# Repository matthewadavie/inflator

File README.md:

# Inflator V3
## Background
I like four wheel driving. I dislike having to sit in the sun to inflate my tyres manually.

Unfortunately the only option (commercially) is on the order of > $300. That is excessive. It can be cheaper.

## Requirements
* Input Voltage: 6V - 18V (nominal)
* Input Voltage: 4V - 30V (transient)
* Functions:
  - HSD/FET gate drive for compressor control & solenoid activation
  - ESP32 for wireless comms (originally wanted STM32 but decided that I would rather control the pressure from webapp on phone)
  - OLED to display pressure readings

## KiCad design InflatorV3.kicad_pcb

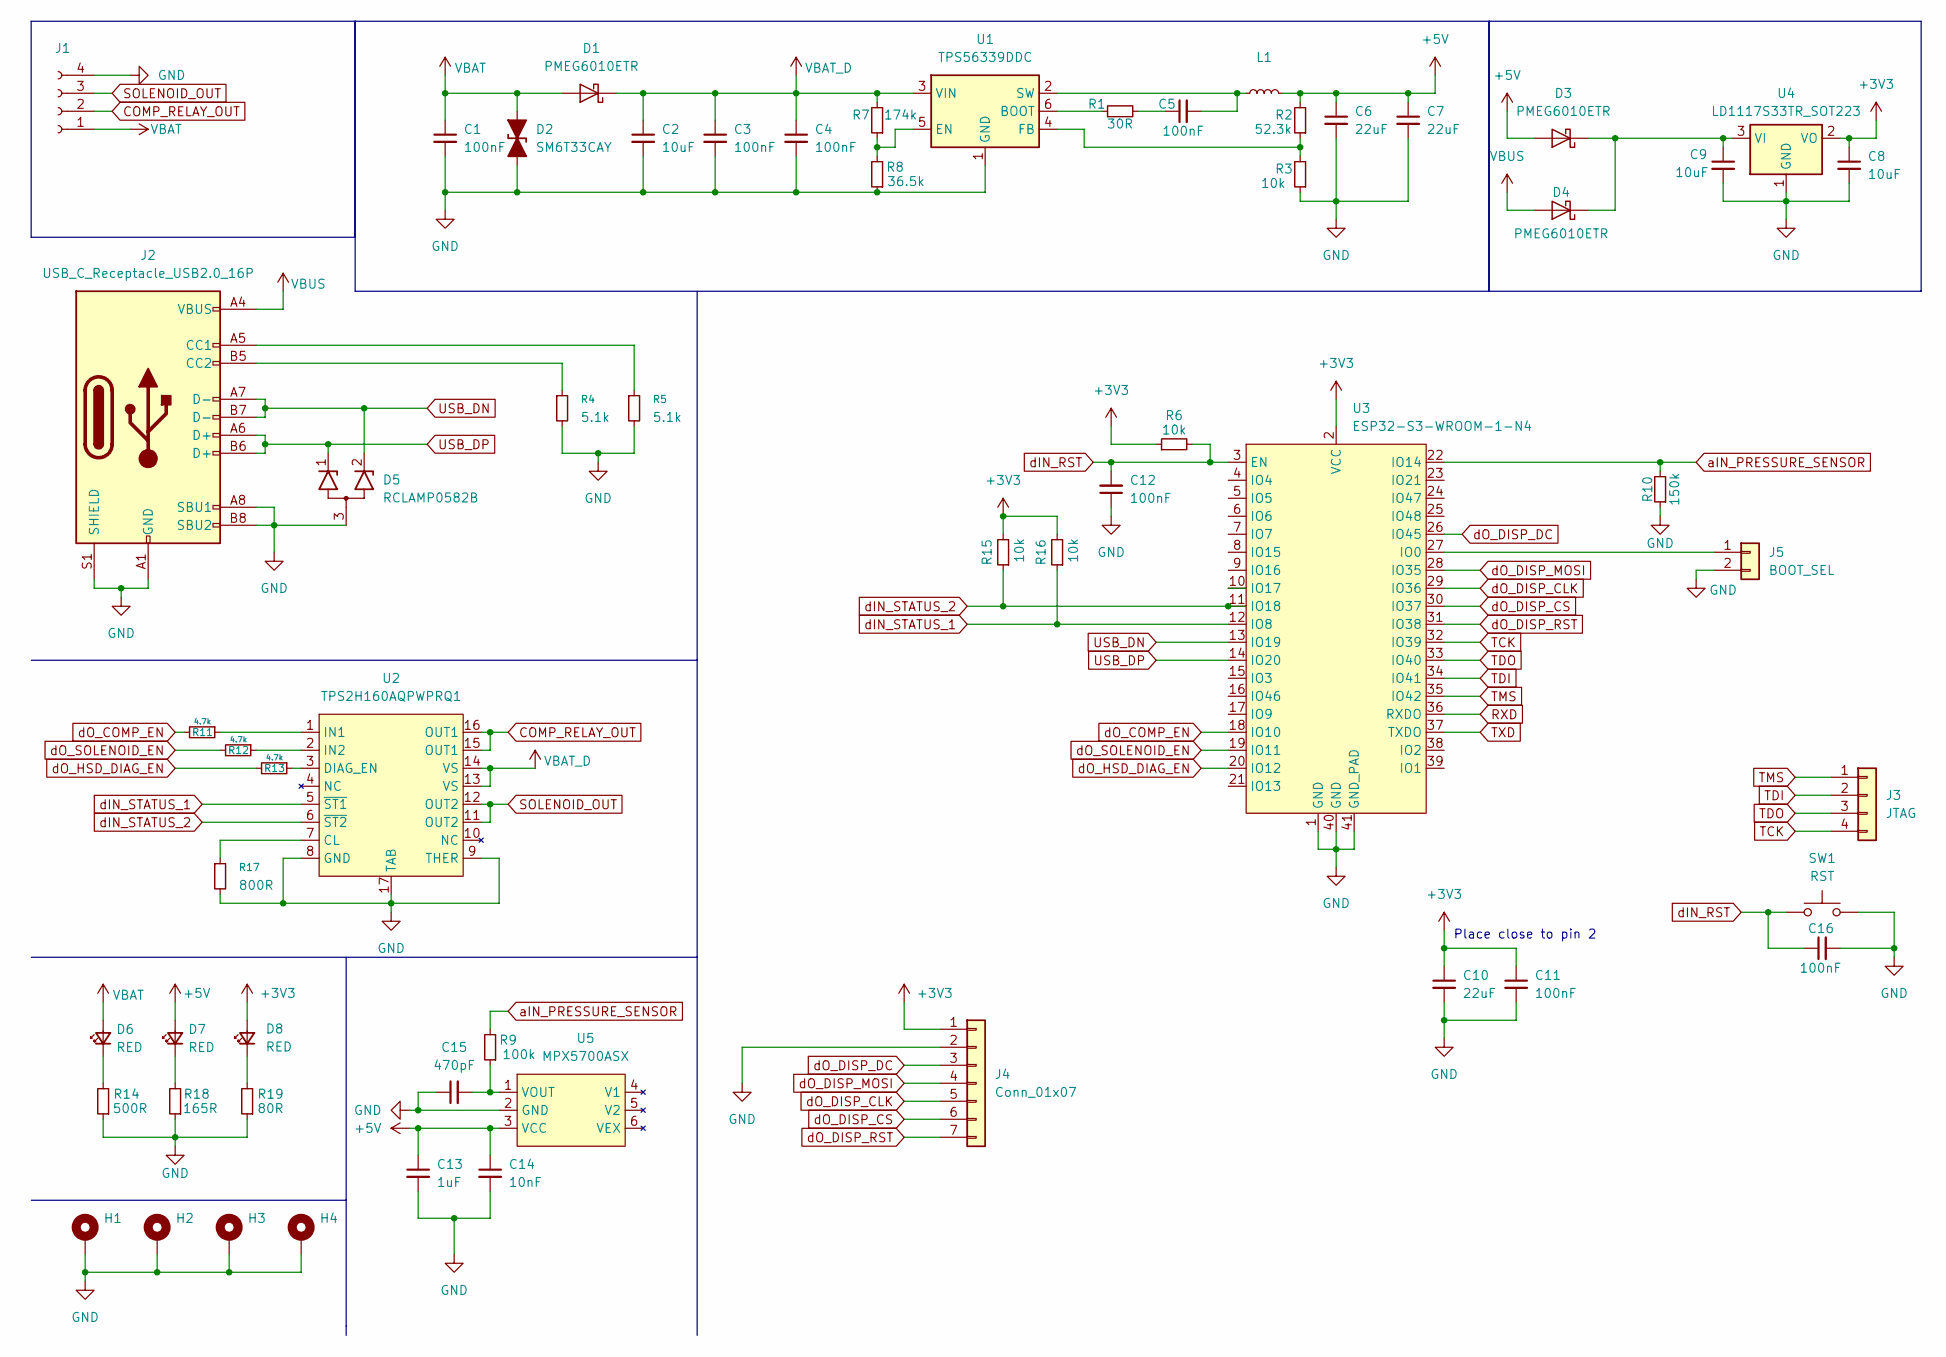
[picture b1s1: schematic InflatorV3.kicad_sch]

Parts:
C1, C11, C12: 100nF; C_1206_3216Metric_Pad1.33x1.80mm_HandSolder
C2: 10uF; C_1206_3216Metric_Pad1.33x1.80mm_HandSolder
C3, C4, C5, C16: 100nF; C_0805_2012Metric_Pad1.18x1.45mm_HandSolder
C6, C7, C10: 22uF; C_1206_3216Metric_Pad1.33x1.80mm_HandSolder
C8, C9: 10uF; C_0805_2012Metric_Pad1.18x1.45mm_HandSolder
C13: 1uF; C_0805_2012Metric_Pad1.18x1.45mm_HandSolder
C14: 10nF; C_0805_2012Metric_Pad1.18x1.45mm_HandSolder
C15: 470pF; C_0805_2012Metric_Pad1.18x1.45mm_HandSolder
D1, D3, D4: PMEG6010ETR; D_SOD-123F
D2: SM6T33CAY; D_SMB_Handsoldering
D5: RCLAMP0582B; SOT-416
D6, D7, D8: RED; LED_0805_2012Metric_Pad1.15x1.40mm_HandSolder
H1, H2, H3, H4: MountingHole_Pad; MountingHole_3.2mm_M3_DIN965_Pad_TopBottom
J1: Molex_Micro-Fit_3.0_43650-0400_1x04_P3.00mm_Horizontal
J2: USB_C_Receptacle_USB2.0_16P; USB_C_Receptacle_GCT_USB4105-xx-A_16P_TopMnt_Horizontal
J3: JTAG; PinHeader_1x04_P2.54mm_Vertical
J4: Conn_01x07; SM07B-GHS-TB
J5: BOOT_SEL; PinHeader_1x02_P2.54mm_Vertical
L1: 5.6uH; IHLP-2020; MPN IHLP2020CZER5R6M01
R1: 30R; R_0805_2012Metric_Pad1.20x1.40mm_HandSolder
R2: 52.3k; R_0805_2012Metric_Pad1.20x1.40mm_HandSolder
R3, R6, R15, R16: 10k; R_0805_2012Metric_Pad1.20x1.40mm_HandSolder
R4, R5: 5.1k; R_0805_2012Metric_Pad1.20x1.40mm_HandSolder
R7: 174k; R_0805_2012Metric_Pad1.20x1.40mm_HandSolder
R8: 36.5k; R_0805_2012Metric_Pad1.20x1.40mm_HandSolder
R9: 100k; R_0805_2012Metric_Pad1.20x1.40mm_HandSolder
R10: 150k; R_0805_2012Metric_Pad1.20x1.40mm_HandSolder
R11, R12, R13: 4.7k; R_0805_2012Metric_Pad1.20x1.40mm_HandSolder
R14: 500R; R_0805_2012Metric_Pad1.20x1.40mm_HandSolder
R17: 800R; R_0805_2012Metric_Pad1.20x1.40mm_HandSolder
R18: 165R; R_0805_2012Metric_Pad1.20x1.40mm_HandSolder
R19: 80R; R_0805_2012Metric_Pad1.20x1.40mm_HandSolder
SW1: RST; PTS526; MPN PTS526SM15SMTR2 LFS
U1: TPS56339DDC; SOT-23-6
U2: TPS2H160AQPWPRQ1; HTSSOP-16-1EP_4.4x5mm_P0.65mm_EP3.4x5mm_Mask2.66x2.46mm; MPN TPS2H160AQPWPRQ1
U3: ESP32-S3-WROOM-1-N4; ESP32-S3-WROOM-1; MPN ESP32-S3-WROOM-1-N4
U4: LD1117S33TR_SOT223; SOT-223-3_TabPin2
U5: MPX5700ASX; MPN MPX5700ASX

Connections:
+3V3: C8.1, C10.1, C11.1, D8.2 (A), J4.1, R6.1, R15.2, R16.2, U3.2 (VCC), U4.2 (VO)
+5V: C6.1, C7.1, C13.1, C14.1, D3.2 (A), D7.2 (A), L1.2, R2.2, U5.3 (VCC)
COMP_RELAY_OUT: J1.2, U2.15 (OUT1), U2.16 (OUT1)
GND: C1.2, C2.2, C3.2, C4.2, C6.2, C7.2, C8.2, C9.2, C10.2, C11.2, C12.1, C13.2, C14.2, C15.1, C16.2, D2.1 (A1), D5.3 (A), H1.1, H2.1, H3.1, H4.1, J1.4, J2.A1 (GND), J2.A8 (SBU1), J2.A12 (GND), J2.B1 (GND), J2.B8 (SBU2), J2.B12 (GND), J2.S1 (SHIELD), J4.2, J5.2, R3.1, R4.2, R5.2, R8.1, R10.1, R14.1, R17.2, R18.1, R19.1, SW1.2, U1.1 (GND), U2.8 (GND), U2.9 (THER), U2.17 (TAB), U3.1 (GND), U3.40 (GND), U3.41 (GND_PAD), U4.1 (GND), U5.2 (GND)
unnamed: C5.1, R1.2
unnamed: C9.1, D3.1 (K), D4.1 (K), U4.3 (VI)
unnamed: D6.1 (K), R14.2
unnamed: D7.1 (K), R18.2
unnamed: D8.1 (K), R19.2
unnamed: J2.A5 (CC1), R5.1
unnamed: J2.B5 (CC2), R4.1
unnamed: J5.1, U3.27 (IO0)
unnamed: R1.1, U1.6 (BOOT)
unnamed: R7.1, R8.2, U1.5 (EN)
unnamed: R2.1, R3.2, U1.4 (FB)
unnamed: C5.2, L1.1, U1.2 (SW)
unnamed: R17.1, U2.7 (CL)
unnamed: R13.1, U2.3 (DIAG_EN)
unnamed: R11.1, U2.1 (IN1)
unnamed: R12.1, U2.2 (IN2)
unnamed: C15.2, R9.1, U5.1 (VOUT)
RXD: U3.36 (RXDO)
SOLENOID_OUT: J1.3, U2.11 (OUT2), U2.12 (OUT2)
TCK: J3.4, U3.32 (IO39)
TDI: J3.2, U3.34 (IO41)
TDO: J3.3, U3.33 (IO40)
TMS: J3.1, U3.35 (IO42)
TXD: U3.37 (TXDO)
USB_DN: D5.2 (K2), J2.A7 (D-), J2.B7 (D-), U3.13 (IO19)
USB_DP: D5.1 (K1), J2.A6 (D+), J2.B6 (D+), U3.14 (IO20)
VBAT: C1.1, D1.2 (A), D2.2 (A2), D6.2 (A), J1.1
VBAT_D: C2.1, C3.1, C4.1, D1.1 (K), R7.2, U1.3 (VIN), U2.13 (VS), U2.14 (VS)
VBUS: D4.2 (A), J2.A4 (VBUS), J2.A9 (VBUS), J2.B4 (VBUS), J2.B9 (VBUS)
aIN_PRESSURE_SENSOR: R9.2, R10.2, U3.22 (IO14)
dIN_RST: C12.2, C16.1, R6.2, SW1.1, U3.3 (EN)
dIN_STATUS_1: R16.1, U2.5 (~ST1), U3.12 (IO8)
dIN_STATUS_2: R15.1, U2.6 (~ST2), U3.11 (IO18)
dO_COMP_EN: R11.2, U3.18 (IO10)
dO_DISP_CLK: J4.5, U3.29 (IO36)
dO_DISP_CS: J4.6, U3.30 (IO37)
dO_DISP_DC: J4.3, U3.26 (IO45)
dO_DISP_MOSI: J4.4, U3.28 (IO35)
dO_DISP_RST: J4.7, U3.31 (IO38)
dO_HSD_DIAG_EN: R13.2, U3.20 (IO12)
dO_SOLENOID_EN: R12.2, U3.19 (IO11)

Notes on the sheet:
Place close to pin 2

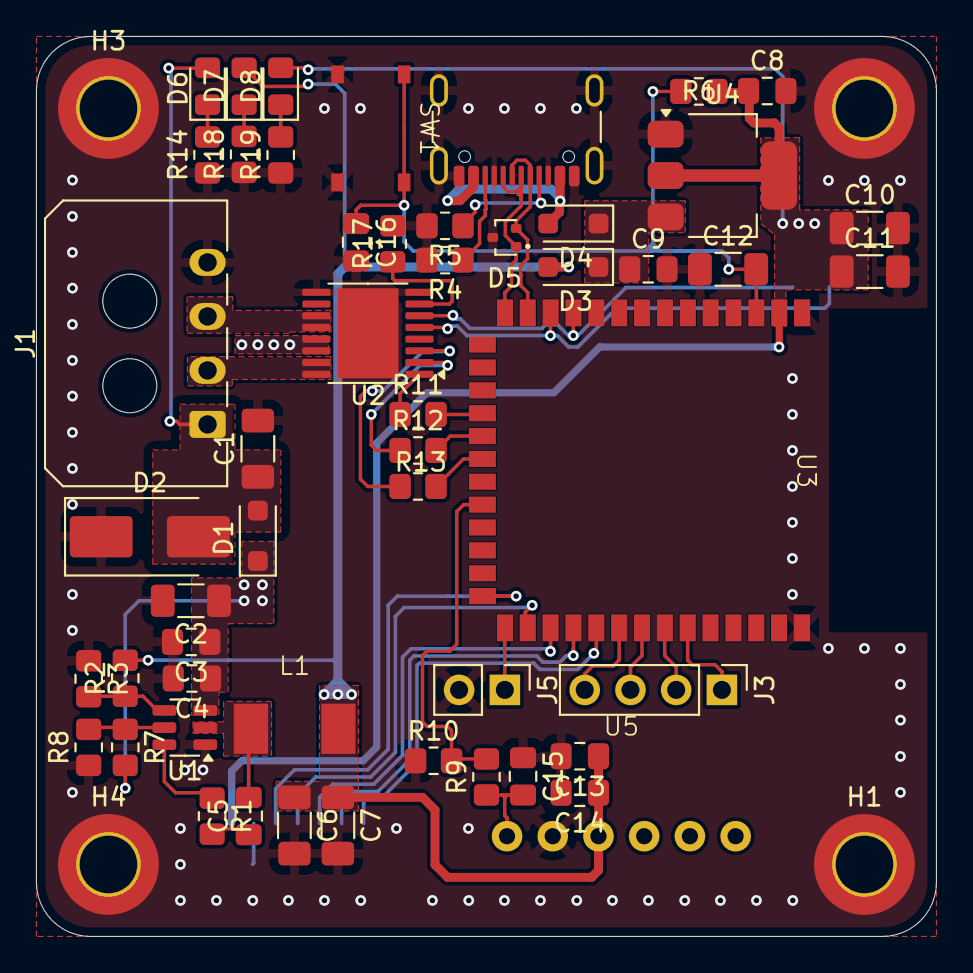
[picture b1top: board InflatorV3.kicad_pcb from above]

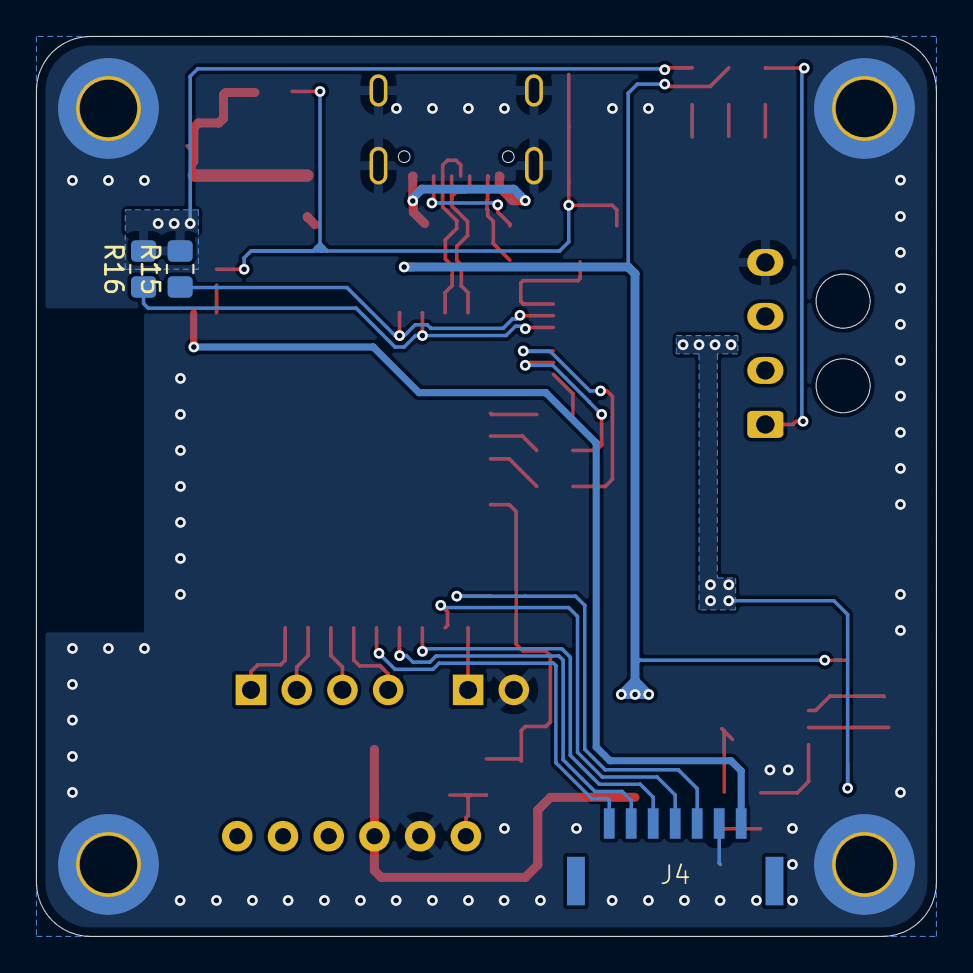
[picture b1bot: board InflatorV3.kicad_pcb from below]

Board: 2 copper layers, 50.0 x 50.0 mm, 59 parts (3 on the bottom side), 43 nets.
